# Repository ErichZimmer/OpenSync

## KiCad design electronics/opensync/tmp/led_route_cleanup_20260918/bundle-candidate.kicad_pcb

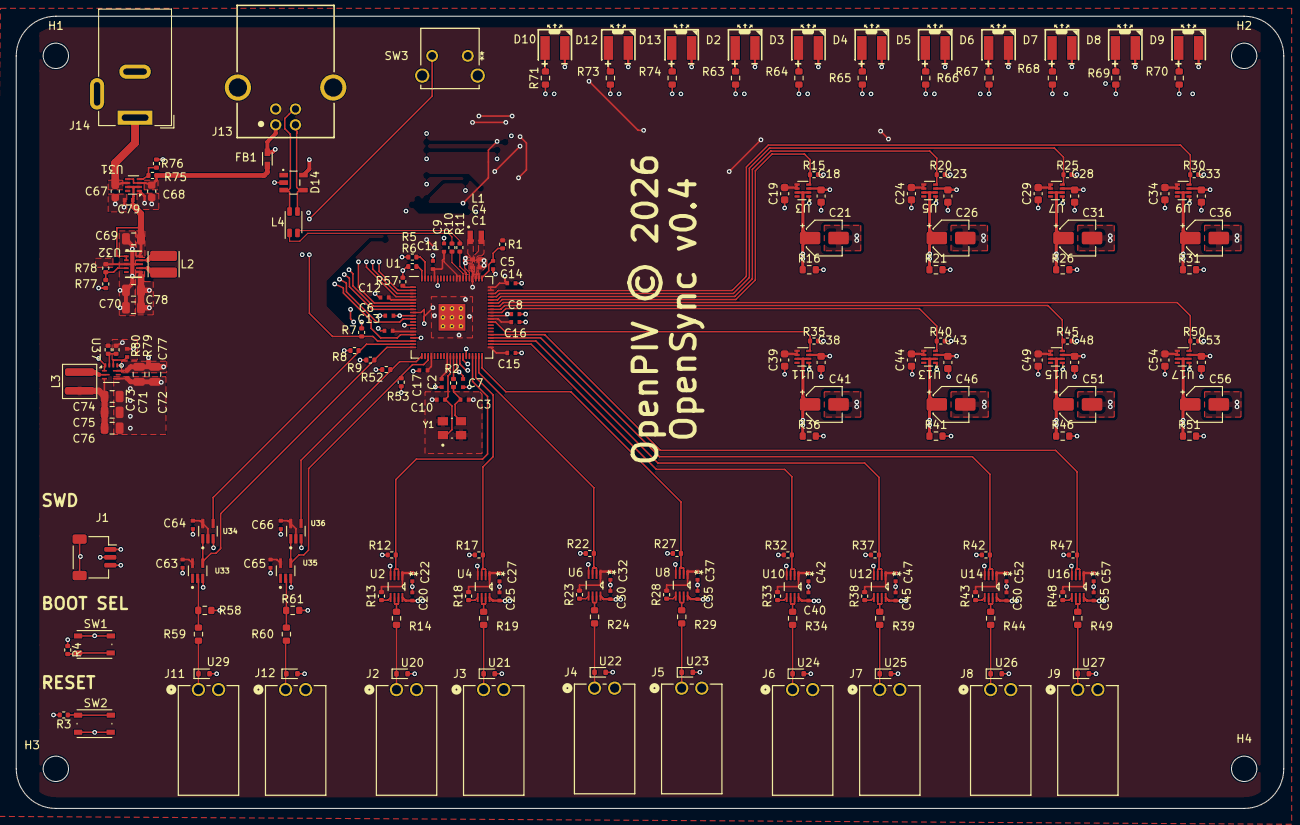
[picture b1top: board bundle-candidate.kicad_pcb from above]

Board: 4 copper layers, 160.0 x 100.0 mm, 221 parts (0 on the bottom side), 114 nets.

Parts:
C1, C4, C5: 4.7u; C_0402_1005Metric_small_pads
C2, C3: 15p; C_0402_1005Metric_small_pads
C6, C7, C8, C9, C10, C11, C12, C13, C14, C15, C16, C17, C20, C22, C25, C27, C30, C32, C35, C37, C40, C42, C45, C47, C50, C52, C55, C57, C63, C64, C65, C66, C79: 100n; C_0402_1005Metric_small_pads
C18, C19, C23, C24, C28, C29, C33, C34, C38, C39, C43, C44, C48, C49, C53, C54, C67, C68: 1u; C_0603_1608Metric
C21, C26, C31, C36, C41, C46, C51, C56: 22u; CP_Elec_4x5.4
C69, C71, C72: 10u; C_0805_2012Metric
C70, C74, C75, C76, C78: 22u; C_0805_2012Metric
C73: 2.2n; C_0402_1005Metric_small_pads
C77: 470n; C_0402_1005Metric_small_pads
D2, D3, D4, D5, D6, D7, D8, D9, D10, D12, D13: LED; LED-SMD_L4.0-W3.6_A67F-U2BA-1-3A4B-30-R33
D14: 5V; WE-TVS_SOT23-5L
FB1: 0603_W2.6_742792641; FB_Wurth_WE-CBF-0603_W2.6
H1, H2, H3, H4: MountingHole; MountingHole_3.2mm_M3_ISO7380
J1: SM03B-SRSS-TB; JST_SH_SM03B-SRSS-TB_1x03-1MP_P1.00mm_Horizontal
J2, J3, J4, J5, J6, J7, J8, J9, J11, J12: 705530001; CONN_705530001_02_MOL
J13: 61400416121
J14: Barrel_Jack_Switch; BarrelJack_Wuerth_6941xx301002
L1: 3.3u; L_pol_2016
L2: 470n; L_Wuerth_MAPI-3020
L3: 2.2u; L_Wuerth_MAPI-4020
L4: Choke_Wurth_WE-CNSW_744232090; L_CommonMode_Wurth_WE-CNSW-1206
R1: 33; R_0402_1005Metric
R2, R3, R4: 1k; R_0402_1005Metric
R5, R6, R7, R8, R9, R12, R15, R17, R20, R22, R25, R27, R30, R32, R35, R37, R40, R42, R45, R47, R50, R52, R53, R57: 10k; R_0402_1005Metric
R10, R11: 27; R_0402_1005Metric
R13, R18, R23, R28, R33, R38, R43, R48: 47k; R_0402_1005Metric
R14, R19, R24, R29, R34, R39, R44, R49: 39; R_0603_1608Metric
R16, R21, R26, R31, R36, R41, R46, R51, R58, R61: 10k; R_0603_1608Metric
R59, R60: 100; R_0603_1608Metric
R63, R64, R65, R66, R67, R68, R69, R70, R71, R73, R74: 470; R_0603_1608Metric
R75: 301k; R_0402_1005Metric
R76: 100k; R_0402_1005Metric
R77: 806k; R_0402_1005Metric
R78: 91k; R_0402_1005Metric
R79: 4.99k; R_0402_1005Metric
R80: 15.6k; R_0402_1005Metric
SW1, SW2: SW_Push; SW_Push_1P1T_NO_Vertical_Wuerth_434133025816
SW3: 2-1825027-0; SW2_1825027-G_TEC
U1: RP2354_80QFN; RP2350-QFN-80-1EP_10x10_P0.4mm_EP3.4x3.4mm_ThermalVias
U2, U4, U6, U8, U10, U12, U14, U16: SN74LVC2T45DCUR; DCU8
U3, U5, U7, U9, U11, U13, U15, U17, U31: TPS2116DRL; SOT-583-8
U20, U21, U22, U23, U24, U25, U26, U27, U29, U30: TPD1E05U06DYA; D_SOD-523
U32: TPS63802DLAR; DLA0010A
U33, U35: SN74LVC1G17DCKR; SOT65P210X110-5N
U34, U36: 74LVC1G86; SOT65P210X110-5N
U37: TPS62912; Texas_RPU0010A_VQFN-HR-10_2x2mm_P0.5mm
Y1: ABM8-272-T3; XTAL_ABM8-272-T3

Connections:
+1V1: C4.1, C6.1, C7.1, C8.1, L1.1, U1.10 (DVDD), U1.32 (DVDD), U1.51 (DVDD), U1.65 (VREG_FB)
+3V3: C1.1, C9.1, C10.1, C11.1, C12.1, C13.1, C14.1, C15.1, C16.1, C17.1, C19.2, C22.2, C24.2, C27.2, C29.2, C32.2, C34.2, C37.2, C39.2, C42.2, C44.2, C47.2, C49.2, C52.2, C54.2, C57.2, C63.1, C64.1, C65.1, C66.1, C74.2, C75.2, C76.2, L3.2, R1.1, R13.1, R18.1, R23.1, R28.1, R33.1, R38.1, R43.1, R48.1, R80.2, SW3.1, U1.5 (IOVDD), U1.15 (IOVDD), U1.24 (IOVDD), U1.29 (IOVDD), U1.41 (IOVDD), U1.50 (IOVDD), U1.59 (ADC_AVDD), U1.60 (IOVDD), U1.64 (VREG_VIN), U1.68 (USB_OTP_VDD), U1.69 (QSPI_IOVDD), U1.76 (IOVDD), U2.1 (VCCA), U3.5 (MODE), U3.6 (VIN2), U4.1 (VCCA), U5.5 (MODE), U5.6 (VIN2), U6.1 (VCCA), U7.5 (MODE), U7.6 (VIN2), U8.1 (VCCA), U9.5 (MODE), U9.6 (VIN2), U10.1 (VCCA), U11.5 (MODE), U11.6 (VIN2), U12.1 (VCCA), U13.5 (MODE), U13.6 (VIN2), U14.1 (VCCA), U15.5 (MODE), U15.6 (VIN2), U16.1 (VCCA), U17.5 (MODE), U17.6 (VIN2), U33.5 (VCC), U34.2, U34.5 (VCC), U35.5 (VCC), U36.2, U36.5 (VCC), U37.3 (VO)
+5V: C18.2, C23.2, C28.2, C33.2, C38.2, C43.2, C48.2, C53.2, C70.2, C71.2, C72.2, C73.2, C78.2, R77.2, U3.3 (VIN1), U5.3 (VIN1), U7.3 (VIN1), U9.3 (VIN1), U11.3 (VIN1), U13.3 (VIN1), U15.3 (VIN1), U17.3 (VIN1), U32.6 (VOUT), U37.1 (EN/SYNC), U37.6 (VIN), U37.10 (S-CONF)
/IN_G: R53.1, U1.23 (GPIO23), U35.4 (Y), U36.1
/IN_G_INV: R52.1, U1.21 (GPIO21), U36.4
/IN_T: R9.1, U1.20 (GPIO20), U33.4 (Y), U34.1
/IN_T_INV: R8.1, U1.19 (GPIO19), U34.4
/Indicator Panel/BTN_START: R7.1, SW3.2, U1.18 (GPIO18)
/Indicator Panel/LED_A: R70.1, U1.2 (GPIO5)
/Indicator Panel/LED_ACTIVE: R71.1, U1.17 (GPIO17)
/Indicator Panel/LED_B: R69.1, U1.3 (GPIO6)
/Indicator Panel/LED_C: R68.1, U1.4 (GPIO7)
/Indicator Panel/LED_D: R67.1, U1.6 (GPIO8)
/Indicator Panel/LED_E: R66.1, U1.7 (GPIO9)
/Indicator Panel/LED_F: R65.1, U1.8 (GPIO10)
/Indicator Panel/LED_G: R64.1, U1.9 (GPIO11)
/Indicator Panel/LED_GATE: R74.1, U1.13 (GPIO14)
/Indicator Panel/LED_H: R63.1, U1.11 (GPIO12)
/Indicator Panel/LED_TRIG: R73.1, U1.16 (GPIO16)
/Microcontroller Circuitry/QSPI_SS: R4.1, U1.75 (QSPI_SS)
/Microcontroller Circuitry/RUN: SW2.2, U1.35 (RUN)
/Microcontroller Circuitry/SIG_CLOCK: R6.2, U1.80 (GPIO3)
/Microcontroller Circuitry/SIG_GATE_INT: R57.2, U1.1 (GPIO4)
/Microcontroller Circuitry/SIG_T0: R5.2, U1.79 (GPIO2)
/Microcontroller Circuitry/SWCLK: J1.1, U1.33 (SWCLK)
/Microcontroller Circuitry/SWD: J1.3, U1.34 (SWD)
/Microcontroller Circuitry/USB_D+: L4.1, R10.1
/Microcontroller Circuitry/USB_D-: L4.4, R11.1
/Microcontroller Circuitry/VREG_LX: L1.2, U1.63 (VREG_LX)
/Microcontroller Circuitry/XIN: C2.2, U1.30 (XIN), Y1.1
/Microcontroller Circuitry/XOUT: R2.2, U1.31 (XOUT)
/OUT_A: R12.1, U1.37 (GPIO29), U2.2 (A1), U2.3 (A2)
/OUT_B: R17.1, U1.38 (GPIO30), U4.2 (A1), U4.3 (A2)
/OUT_C: R22.1, U1.39 (GPIO31), U6.2 (A1), U6.3 (A2)
/OUT_D: R27.1, U1.40 (GPIO32), U8.2 (A1), U8.3 (A2)
/OUT_E: R32.1, U1.42 (GPIO33), U10.2 (A1), U10.3 (A2)
/OUT_F: R37.1, U1.43 (GPIO34), U12.2 (A1), U12.3 (A2)
/OUT_G: R42.1, U1.44 (GPIO35), U14.2 (A1), U14.3 (A2)
/OUT_H: R47.1, U1.45 (GPIO36), U16.2 (A1), U16.3 (A2)
/Output Channel 1/VOUT: C20.2, C21.1, R16.1, U2.8 (VCCB), U3.2 (VOUT), U3.7 (VOUT)
/Output Channel 2/VOUT: C25.2, C26.1, R21.1, U4.8 (VCCB), U5.2 (VOUT), U5.7 (VOUT)
/Output Channel 3/VOUT: C30.2, C31.1, R26.1, U6.8 (VCCB), U7.2 (VOUT), U7.7 (VOUT)
/Output Channel 4/VOUT: C35.2, C36.1, R31.1, U8.8 (VCCB), U9.2 (VOUT), U9.7 (VOUT)
/Output Channel 5/VOUT: C40.2, C41.1, R36.1, U10.8 (VCCB), U11.2 (VOUT), U11.7 (VOUT)
/Output Channel 6/VOUT: C45.2, C46.1, R41.1, U12.8 (VCCB), U13.2 (VOUT), U13.7 (VOUT)
/Output Channel 7/VOUT: C50.2, C51.1, R46.1, U14.8 (VCCB), U15.2 (VOUT), U15.7 (VOUT)
/Output Channel 8/VOUT: C55.2, C56.1, R51.1, U16.8 (VCCB), U17.2 (VOUT), U17.7 (VOUT)
/Power Interface/VDC: C67.2, J14.1, U31.6 (VIN2)
/Power Interface/VOUT: C69.2, C79.1, U31.2 (VOUT), U31.7 (VOUT), U32.1 (EN), U32.2 (MODE), U32.10 (VIN)
/USB Interface/VBUS_RAW: D14.5 (VDD), FB1.2, J13.1 (VBUS)
/VSEL_A: R15.1, U1.55 (GPIO44_ADC4), U3.4 (PR1)
/VSEL_B: R20.1, U1.56 (GPIO45_ADC5), U5.4 (PR1)
/VSEL_C: R25.1, U1.57 (GPIO46_ADC6), U7.4 (PR1)
/VSEL_D: R30.1, U1.58 (GPIO47_ADC7), U9.4 (PR1)
/VSEL_E: R35.1, U1.49 (GPIO40_ADC0), U11.4 (PR1)
/VSEL_F: R40.1, U1.52 (GPIO41_ADC1), U13.4 (PR1)
/VSEL_G: R45.1, U1.53 (GPIO42_ADC2), U15.4 (PR1)
/VSEL_H: R50.1, U1.54 (GPIO43_ADC3), U17.4 (PR1)
GND: C1.2, C2.1, C3.1, C4.2, C5.2, C6.2, C7.2, C8.2, C9.2, C10.2, C11.2, C12.2, C13.2, C14.2, C15.2, C16.2, C17.2, C18.1, C19.1, C20.1, C21.2, C22.1, C23.1, C24.1, C25.1, C26.2, C27.1, C28.1, C29.1, C30.1, C31.2, C32.1, C33.1, C34.1, C35.1, C36.2, C37.1, C38.1, C39.1, C40.1, C41.2, C42.1, C43.1, C44.1, C45.1, C46.2, C47.1, C48.1, C49.1, C50.1, C51.2, C52.1, C53.1, C54.1, C55.1, C56.2, C57.1, C63.2, C64.2, C65.2, C66.2, C67.1, C68.1, C69.1, C70.1, C71.1, C72.1, C73.1, C74.1, C75.1, C76.1, C77.1, C78.1, C79.2, D2.1 (K), D3.1 (K), D4.1 (K), D5.1 (K), D6.1 (K), D7.1 (K), D8.1 (K), D9.1 (K), D10.1 (K), D12.1 (K), D13.1 (K), D14.2 (GND), J1.2, J1.MP (MountPin), J2.2, J3.2, J4.2, J5.2, J6.2, J7.2, J8.2, J9.2, J11.2, J12.2, J13.4 (GND), J13.S1, J13.S2, J14.3, R3.2, R5.1, R6.1, R7.2, R8.2, R9.2, R12.2, R15.2, R16.2, R17.2, R20.2, R21.2, R22.2, R25.2, R26.2, R27.2, R30.2, R31.2, R32.2, R35.2, R36.2, R37.2, R40.2, R41.2, R42.2, R45.2, R46.2, R47.2, R50.2, R51.2, R52.2, R53.2, R57.1, R58.2, R61.2, R76.2, R78.2, R79.2, SW1.1, U1.62 (VREG_PGND), U1.81 (GND), U2.4 (GND), U3.1 (GND), U4.4 (GND), U5.1 (GND), U6.4 (GND), U7.1 (GND), U8.4 (GND), U9.1 (GND), U10.4 (GND), U11.1 (GND), U12.4 (GND), U13.1 (GND), U14.4 (GND), U15.1 (GND), U16.4 (GND), U17.1 (GND), U20.2 (GND), U21.2 (GND), U22.2 (GND), U23.2 (GND), U24.2 (GND), U25.2 (GND), U26.2 (GND), U27.2 (GND), U29.2 (GND), U30.2 (GND), U31.1 (GND), U32.3 (AGND), U32.8 (GND), U33.3 (GND), U34.3 (GND), U35.3 (GND), U36.3 (GND), U37.4 (PGND), U37.7 (PSNS), Y1.2 (GND), Y1.4 (GND)
unnamed: C3.2, R2.1, Y1.3
unnamed: D2.2 (A), R63.2
unnamed: D3.2 (A), R64.2
unnamed: D4.2 (A), R65.2
unnamed: D5.2 (A), R66.2
unnamed: D6.2 (A), R67.2
unnamed: D7.2 (A), R68.2
unnamed: D8.2 (A), R69.2
unnamed: D9.2 (A), R70.2
unnamed: D10.2 (A), R71.2
unnamed: D12.2 (A), R73.2
unnamed: D13.2 (A), R74.2
unnamed: D14.3 (I/O_1), J13.3 (D+), L4.2
unnamed: D14.4 (I/O_2), J13.2 (D-), L4.3
unnamed: R3.1, SW2.1
unnamed: R4.2, SW1.2
unnamed: R11.2, U1.66 (USB_DM)
unnamed: R10.2, U1.67 (USB_DP)
unnamed: C5.1, R1.2, U1.61 (VREG_AVDD)
unnamed: R14.1, U2.6 (B2), U2.7 (B1)
unnamed: R13.2, U2.5 (DIR)
unnamed: R19.1, U4.6 (B2), U4.7 (B1)
unnamed: R18.2, U4.5 (DIR)
unnamed: R24.1, U6.6 (B2), U6.7 (B1)
unnamed: R23.2, U6.5 (DIR)
unnamed: R29.1, U8.6 (B2), U8.7 (B1)
unnamed: R28.2, U8.5 (DIR)
unnamed: R34.1, U10.6 (B2), U10.7 (B1)
unnamed: R33.2, U10.5 (DIR)
unnamed: R39.1, U12.6 (B2), U12.7 (B1)
unnamed: R38.2, U12.5 (DIR)
unnamed: R44.1, U14.6 (B2), U14.7 (B1)
unnamed: R43.2, U14.5 (DIR)
unnamed: R49.1, U16.6 (B2), U16.7 (B1)
unnamed: R48.2, U16.5 (DIR)
unnamed: J2.1, R14.2, U20.1 (I/O)
unnamed: J3.1, R19.2, U21.1 (I/O)
unnamed: J4.1, R24.2, U22.1 (I/O)
unnamed: J5.1, R29.2, U23.1 (I/O)
unnamed: J6.1, R34.2, U24.1 (I/O)
unnamed: J7.1, R39.2, U25.1 (I/O)
unnamed: J8.1, R44.2, U26.1 (I/O)
unnamed: J9.1, R49.2, U27.1 (I/O)
unnamed: J11.1, R59.1, U29.1 (I/O)
unnamed: J12.1, R60.1, U30.1 (I/O)
unnamed: R75.2, R76.1, U31.4 (PR1)
unnamed: R77.1, R78.1, U32.4 (FB)
unnamed: L2.1, U32.9 (L1)
unnamed: L2.2, U32.7 (L2)
unnamed: R58.1, R59.2, U33.2 (A)
unnamed: R60.2, R61.1, U35.2 (A)
unnamed: R79.1, R80.1, U37.9 (FB)
unnamed: C77.2, U37.8 (NR/SS)
unnamed: L3.1, U37.2 (SW)
VBUS: C68.2, FB1.1, R75.1, U31.3 (VIN1), U31.5 (MODE)

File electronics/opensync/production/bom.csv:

Designator,Footprint,Quantity,Value,LCSC Part #
"C1, C4, C5",0402,3,4.7u,C342983
"C10, C11, C12, C13, C14, C15, C16, C17, C20, C22, C25, C27, C30, C32, C35, C37, C40, C42, C45, C47, C50, C52, C55, C57, C6, C61, C65, C66, C7, C79, C8, C9",0402,32,100n,C343042
"C18, C19, C23, C24, C28, C29, C33, C34, C38, C39, C43, C44, C48, C49, C53, C54, C58, C62, C67, C68",0603,20,1u,C76708
"C2, C3",0402,2,15p,C338103
"C21, C26, C31, C36, C41, C46, C51, C56",CP_Elec_4x5.4,8,22u,C2164097
C59,0402,1,100p,C281750
C60,0402,1,1n,C76704
"C69, C70, C74, C75, C76, C78, C80, C81, C82",0805,9,22u,C342717
"C71, C72",0805,2,10u,C342722
C73,0402,1,2.2n,C338081
C77,0402,1,470n,C432936
"D1, D11",X1SON-2_L1.0-W0.6-P0.65-BI,2,ESD701DPYR,C42409125
"D10, D12, D13, D2, D3, D4, D5, D6, D7, D8, D9",LED-SMD_L4.0-W3.6_A67F-U2BA-1-3A4B-30-R33,11,LED,C7545687
D14,WE-TVS_SOT23-5L,1,5V,C5341668
FB1,FB_Wurth_WE-CBF-0603_W2.6,1,0603_W2.6_742792641,C2649308
J1,JST_SH_SM03B-SRSS-TB_1x03-1MP_P1.00mm_Horizontal,1,SM03B-SRSS-TB,C160403
J10,AMPHENOL_61729-0010BLF,1,61729-0010BLF,C598579
J14,BarrelJack_Wuerth_6941xx301002,1,Barrel_Jack_Switch,C5441017
"J15, J16",CONN-TH_705430001,2,Conn_01x02,C127361
"J17, J18, J2, J3, J4, J5, J6, J7, J8, J9",CONN_705530001_02_MOL,10,705530001,C564143
L1,L_pol_2016,1,3.3u,C42411119
L2,L_TDK_TMS252012ALM,1,470n,C24296304
L3,L_Wuerth_MAPI-4020,1,2.2u,C5521727
L4,L_CommonMode_Wurth_WE-CNSW-1206,1,Choke_Wurth_WE-CNSW_744232090,C2649327
L5,L0603,1,7427922808,C2661810
R1,0402,1,33,C844506
"R10, R11",0402,2,27,C4162575
"R12, R15, R17, R20, R22, R25, R27, R30, R32, R35, R37, R40, R42, R45, R47, R5, R50, R57, R6, R62, R7, R72, R8, R82, R84, R9",0402,26,10k,C71617
"R13, R18, R23, R28, R33, R38, R43, R48",0402,8,47k,C482184
"R14, R19, R24, R29, R34, R39, R44, R49",0603,8,39,C544038
"R16, R21, R26, R31, R36, R41, R46, R51, R54",0603,9,10k,C844918
"R2, R3, R4, R81, R83",0402,5,1k,C313354
R55,0603,1,5.6k,C844799
"R63, R64, R65, R66, R67, R68, R69, R70, R71, R73, R74",0603,11,470,C844786
R76,0402,1,100k,C481918
R77,0402,1,806k,C2076627
R78,0402,1,91k,C2086333
R79,0402,1,4.99k,C4010684
R80,0402,1,15.6k,C2075329
"SW1, SW2",SW_Push_1P1T_NO_Vertical_Wuerth_434133025816,2,SW_Push,C5504987
SW3,SW2_1825027-G_TEC,1,2-1825027-0,C590206
U1,RP2350-QFN-80-1EP_10x10_P0.4mm_EP3.4x3.4mm_ThermalVias,1,RP2354_80QFN,C39843328
"U10, U12, U14, U16, U2, U4, U6, U8",DCU8,8,SN74LVC2T45DCUR,C15741
"U11, U13, U15, U17, U3, U31, U5, U7, U9",SOT-583-8,9,TPS2116DRL,C3235557
"U18, U19",SC-70-5_L2.0-W1.3-P0.65-LS2.1-BR,2,TLV3601DCKR,C2974371
"U20, U21, U22, U23, U24, U25, U26, U27",D_SOD-523,8,TPD1E05U06DYA,C3702980
U28,VSSOP-10_L3.0-W3.0-P0.50-LS4.9-BL,1,DAC8563SDGSR,C1554729
U32,DLA0010A,1,TPS63802DLAR,C2845237
U37,Texas_RPU0010A_VQFN-HR-10_2x2mm_P0.5mm,1,TPS62912,C3198056
Y1,XTAL_ABM8-272-T3,1,ABM8-272-T3,C20625731

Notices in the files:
electronics/opensync/tmp/led_route_cleanup_20260918/bundle-candidate.kicad_pcb:
OpenPIV © 2026
